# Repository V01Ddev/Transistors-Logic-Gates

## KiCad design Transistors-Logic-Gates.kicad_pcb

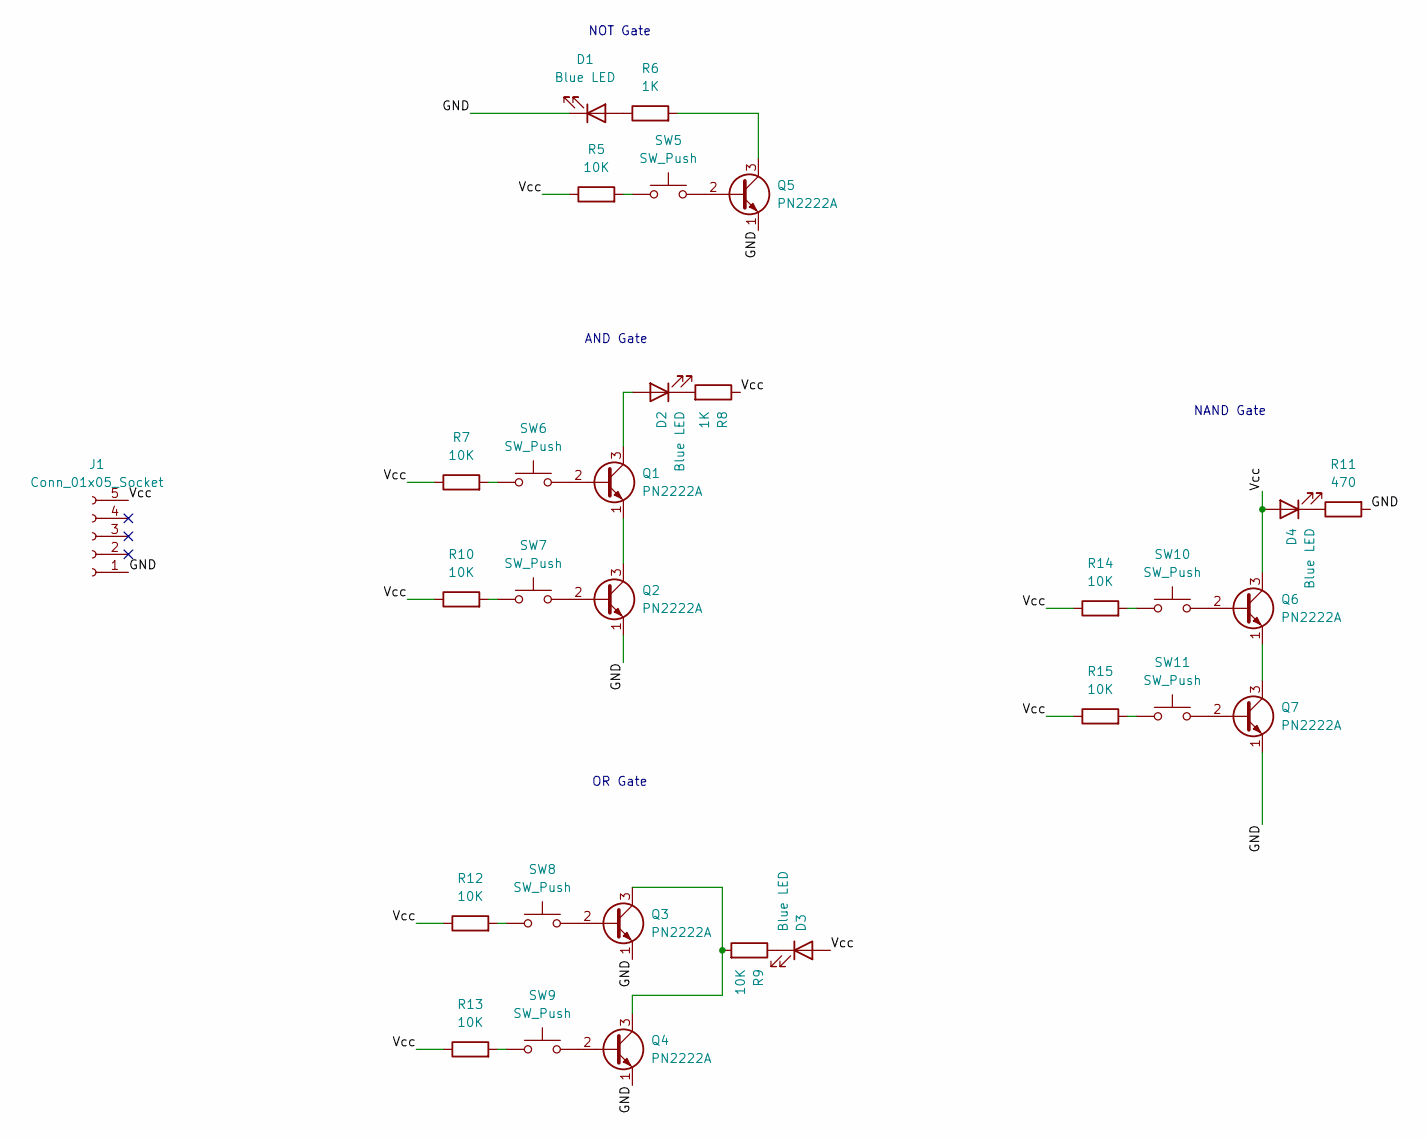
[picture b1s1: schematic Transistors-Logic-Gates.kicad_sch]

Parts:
D1, D2, D3, D4: Blue LED; LED_D1.8mm_W3.3mm_H2.4mm
J1: Conn_01x05_Socket; PinHeader_1x05_P2.54mm_Vertical
Q1, Q2, Q3, Q4, Q5, Q6, Q7: PN2222A; TO-92_Inline
R5, R7, R9, R10, R12, R13, R14, R15: 10K; R_Axial_DIN0204_L3.6mm_D1.6mm_P7.62mm_Horizontal
R6, R8: 1K; R_Axial_DIN0204_L3.6mm_D1.6mm_P7.62mm_Horizontal
R11: 470; R_Axial_DIN0204_L3.6mm_D1.6mm_P7.62mm_Horizontal
SW5, SW6, SW7, SW8, SW9, SW10, SW11: SW_Push; SW_PUSH_6mm_H5mm

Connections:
/GND: D1.1 (K), J1.1, Q2.1 (E), Q3.1 (E), Q4.1 (E), Q5.1 (E), Q7.1 (E), R11.2
/Vcc: D3.2 (A), D4.2 (A), J1.5, Q6.3 (C), R5.1, R7.1, R8.1, R10.1, R12.1, R13.1, R14.1, R15.1
unnamed: D1.2 (A), R6.1
unnamed: D2.2 (A), Q1.3 (C)
unnamed: D2.1 (K), R8.2
unnamed: D3.1 (K), R9.1
unnamed: D4.1 (K), R11.1
unnamed: Q1.2 (B), SW6.2
unnamed: Q1.1 (E), Q2.3 (C)
unnamed: Q2.2 (B), SW7.2
unnamed: Q3.2 (B), SW8.2
unnamed: Q3.3 (C), Q4.3 (C), R9.2
unnamed: Q4.2 (B), SW9.2
unnamed: Q5.2 (B), SW5.2
unnamed: Q5.3 (C), R6.2
unnamed: Q6.2 (B), SW10.2
unnamed: Q6.1 (E), Q7.3 (C)
unnamed: Q7.2 (B), SW11.2
unnamed: R5.2, SW5.1
unnamed: R7.2, SW6.1
unnamed: R10.2, SW7.1
unnamed: R12.2, SW8.1
unnamed: R13.2, SW9.1
unnamed: R14.2, SW10.1
unnamed: R15.2, SW11.1

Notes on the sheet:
AND Gate
NOT Gate
OR Gate
NAND Gate

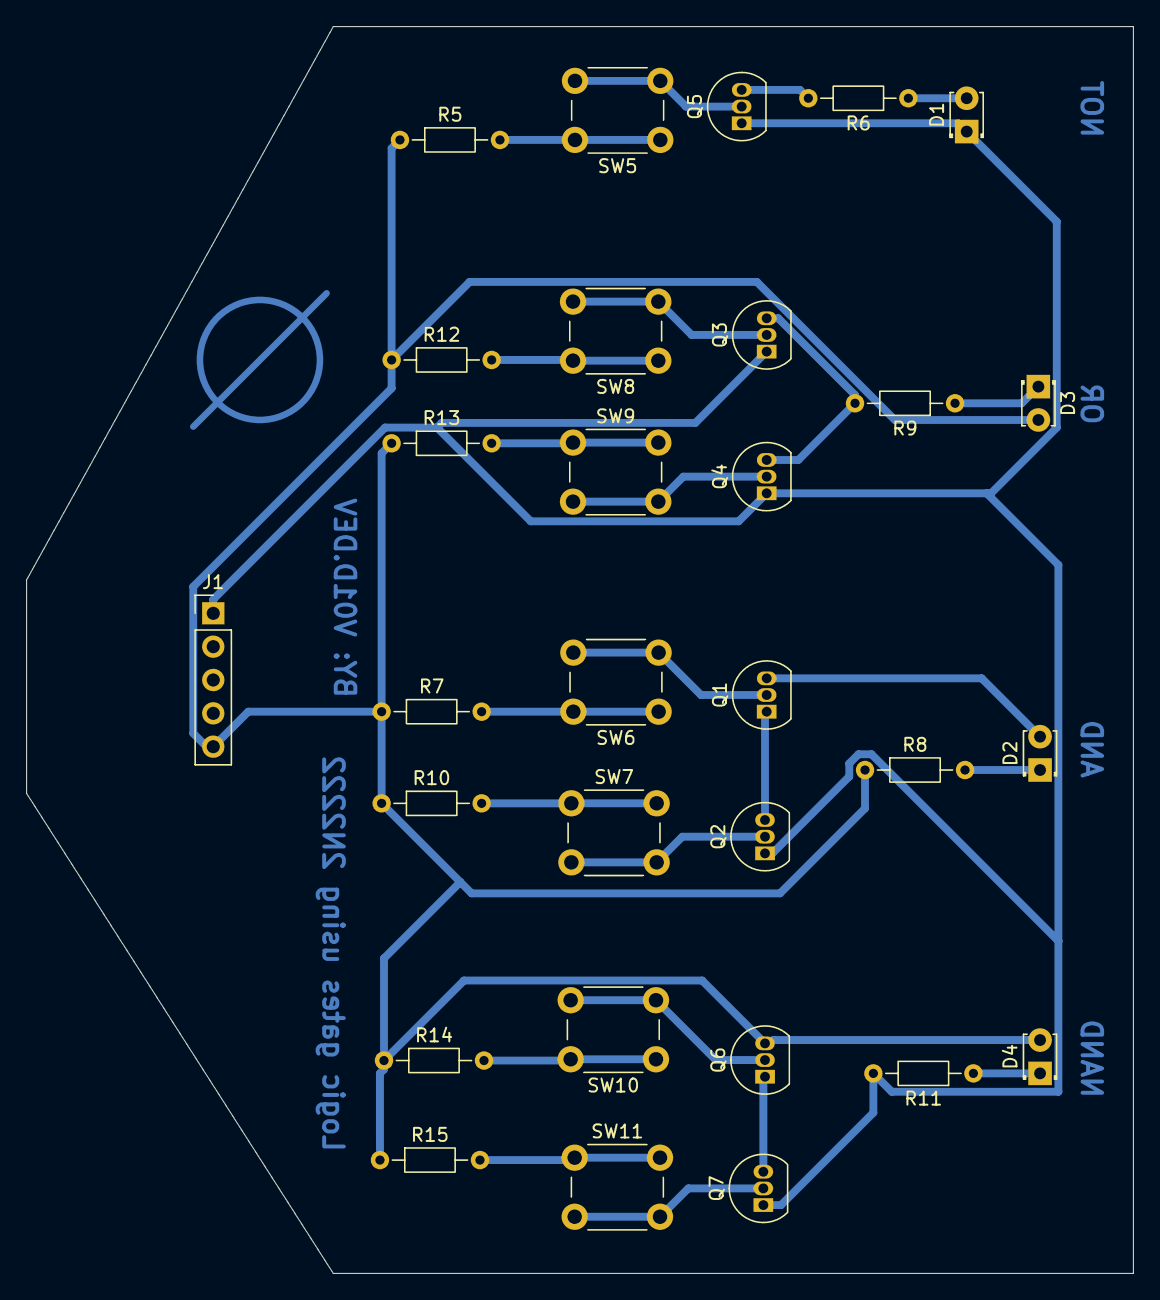
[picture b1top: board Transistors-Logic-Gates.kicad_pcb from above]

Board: 2 copper layers, 84.3 x 95.0 mm, 30 parts (0 on the bottom side), 25 nets.

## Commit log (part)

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2026-05-16 feat: finished schematic
2026-05-16 feat: fixed GND plane, need to change minimums
